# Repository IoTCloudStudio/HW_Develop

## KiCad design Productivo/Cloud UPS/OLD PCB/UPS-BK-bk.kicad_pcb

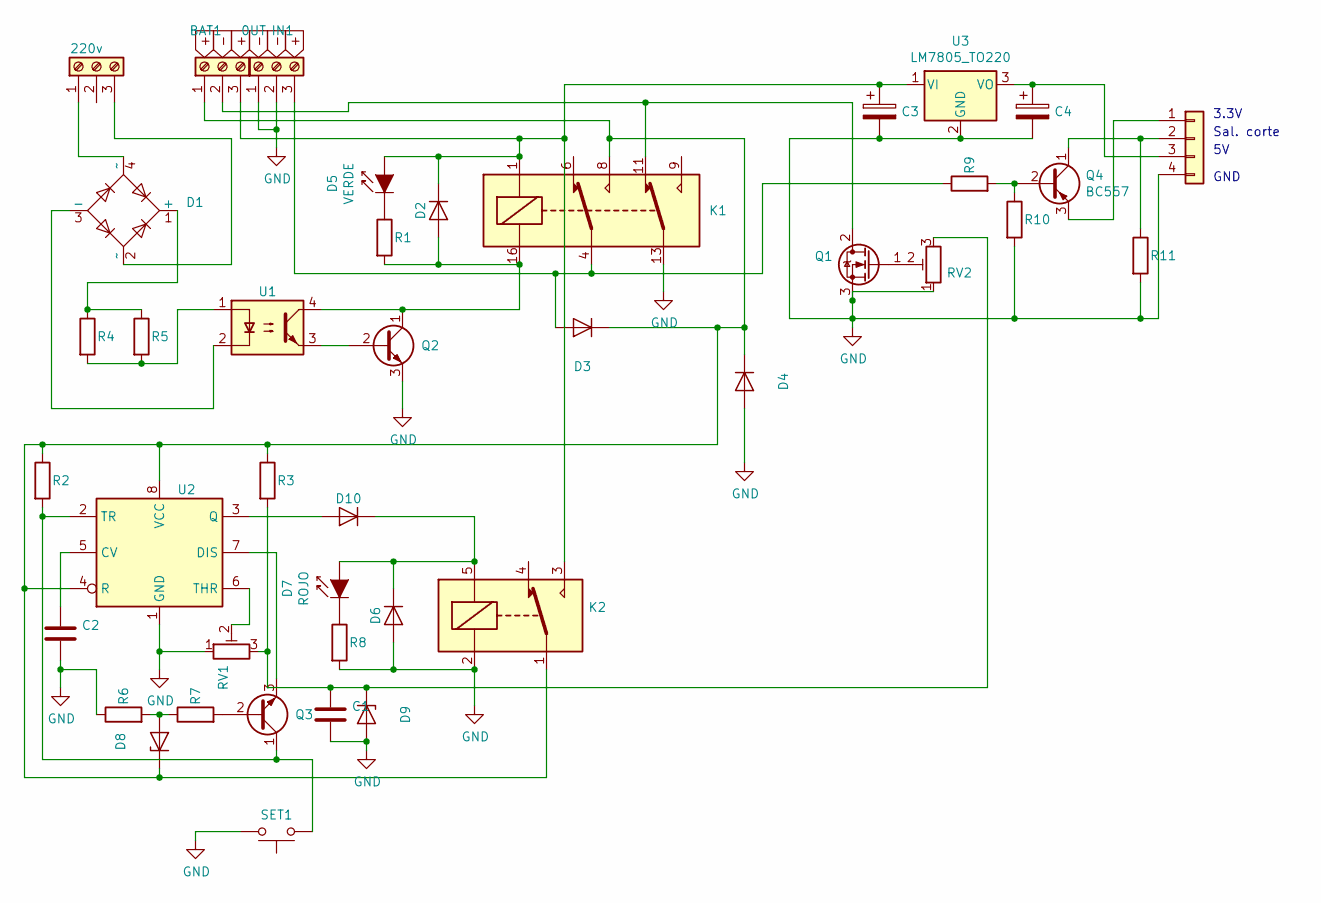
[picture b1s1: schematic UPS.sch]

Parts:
BAT1: 0UT; TerminalBlock_bornier-3_P5.08mm
C1: 100 Nf; C_Axial_L5.1mm_D3.1mm_P7.50mm_Horizontal
C2: 100nF; C_Axial_L5.1mm_D3.1mm_P7.50mm_Horizontal
C3: 33u; C_Radial_D5.0mm_H11.0mm_P2.00mm
C4: 1u; C_Radial_D5.0mm_H11.0mm_P2.00mm
D1: W10G; Diode_Bridge_Round_D9.8mm
D2, D6, D10: 1N4148; D_DO-35_SOD27_P7.62mm_Horizontal
D3, D4: 1N5408; D_DO-201AD_P15.24mm_Horizontal
D5: VERDE; LED_D3.0mm_IRBlack
D7: ROJO; LED_D3.0mm_IRBlack
D8, D9: D_Zener; D_DO-35_SOD27_P7.62mm_Horizontal
IN1: 12V; TerminalBlock_bornier-3_P5.08mm
J1: Conn_01x04; JST_EH_S4B-EH_1x04_P2.50mm_Horizontal
K1: G5V-2; Relay_DPDT_Omron_G5V-2
K2: SANYOU_SRD_Form_C; Relay_SPDT_SANYOU_SRD_Series_Form_C
Q1: IRF540N; TO-220-3_Vertical
Q2, Q3: BC548; TO-92_Inline
Q4: BC557; TO-92_Inline
R1: R; R_Axial_DIN0207_L6.3mm_D2.5mm_P2.54mm_Vertical
R2, R7, R8: 2K2; R_Axial_DIN0204_L3.6mm_D1.6mm_P1.90mm_Vertical
R3: 330; R_Axial_DIN0204_L3.6mm_D1.6mm_P1.90mm_Vertical
R4, R5: 68K; R_Axial_DIN0516_L15.5mm_D5.0mm_P5.08mm_Vertical
R6: 180; R_Axial_DIN0204_L3.6mm_D1.6mm_P1.90mm_Vertical
R9, R10, R11: 10k; R_Axial_DIN0207_L6.3mm_D2.5mm_P2.54mm_Vertical
RV1, RV2: R_POT_TRIM; Potentiometer_Bourns_3386P_Vertical
SET1: SW_Push; SW_SPST_CK_RS282G05A3
U1: PC817; DIP-4_W7.62mm
U2: NE555; DIP-8_W7.62mm_LongPads
U3: LM7805_TO220; TO-220-3_Vertical
j1: 220v; TerminalBlock_bornier-3_P5.08mm

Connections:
GND: C1.2, C2.2, C3.2, C4.2, D4.2 (A), D6.2 (A), D9.2 (A), IN1.1, IN1.2, J1.4, K1.13, K2.2, Q1.3 (S), Q2.3 (E), R6.1, R8.2, R10.2, R11.2, RV1.1, RV2.1, SET1.2, U2.1 (GND), U3.2 (GND); also elsewhere on the board
unnamed 1: BAT1.1, D3.1 (K), D4.1 (K), D8.1 (K), K1.8, K2.1, R2.1, R3.1, U2.4 (R), U2.8 (VCC); also elsewhere on the board
unnamed 2: BAT1.2, K1.11, Q1.2 (D); also elsewhere on the board
unnamed 3: BAT1.3, C3.1, D2.1 (K), D5.2 (A), K1.1, K2.3, U3.1 (VI); also elsewhere on the board
unnamed: C1.1, D9.1 (K), R3.2, RV1.3, RV2.3
unnamed: C2.1, U2.5 (CV)
unnamed: C4.1, J1.3, U3.3 (VO)
unnamed: D1.1 (+), R4.1, R5.1
unnamed: D1.2 (~~), j1.3
unnamed: D1.3 (-), U1.2
unnamed: D1.4 (~~), j1.1
unnamed 11: D2.2 (A), K1.16, Q2.1 (C), R1.2, U1.4; also elsewhere on the board
unnamed 12: D3.2 (A), IN1.3, K1.4, R9.1; also elsewhere on the board
unnamed: D5.1 (K), R1.1
unnamed: D7.1 (K), R8.1
unnamed: D8.2 (A), R6.2, R7.1
unnamed: D6.1 (K), D7.2 (A), D10.1 (K), K2.5
unnamed: D10.2 (A), U2.3 (Q)
unnamed: J1.1, Q4.3 (E)
unnamed: J1.2, Q4.1 (C), R11.1
unnamed: Q1.1 (G), RV2.2
unnamed: Q2.2 (B), U1.3
unnamed: Q3.1 (C), R2.2, SET1.1, U2.2 (TR)
unnamed: Q3.2 (B), R7.2
unnamed: Q3.3 (E), U2.7 (DIS)
unnamed: Q4.2 (B), R9.2, R10.1
unnamed: R4.2, R5.2, U1.1
unnamed: RV1.2, U2.6 (THR)

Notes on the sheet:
3.3V
Sal. corte
GND

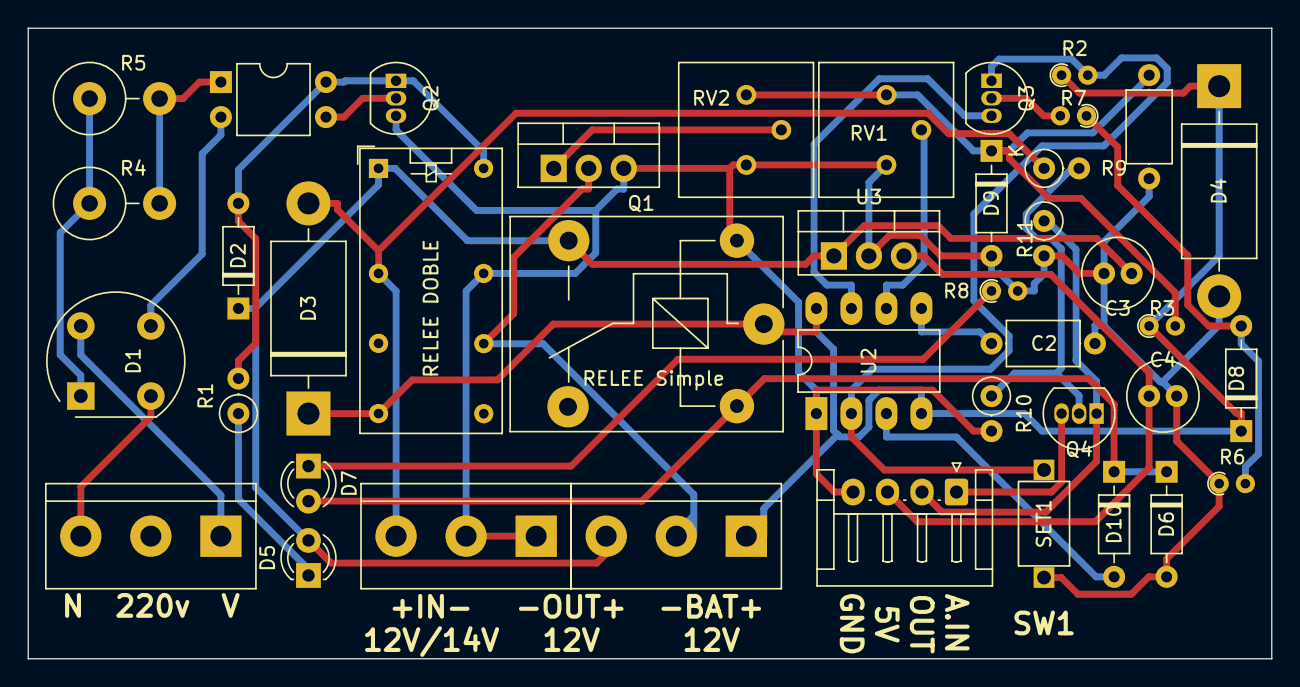
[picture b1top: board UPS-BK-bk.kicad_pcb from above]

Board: 2 copper layers, 90.2 x 45.7 mm, 41 parts (0 on the bottom side), 28 nets.

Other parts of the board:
RELEE DOBLE: G5V-2; Relay_DPDT_Omron_G5V-2

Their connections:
GND: RELEE DOBLE.13; also elsewhere on the board
unnamed 1: RELEE DOBLE.8; also elsewhere on the board
unnamed 2: RELEE DOBLE.11; also elsewhere on the board
unnamed 3: RELEE DOBLE.1; also elsewhere on the board
unnamed 11: RELEE DOBLE.16; also elsewhere on the board
unnamed 12: RELEE DOBLE.4; also elsewhere on the board

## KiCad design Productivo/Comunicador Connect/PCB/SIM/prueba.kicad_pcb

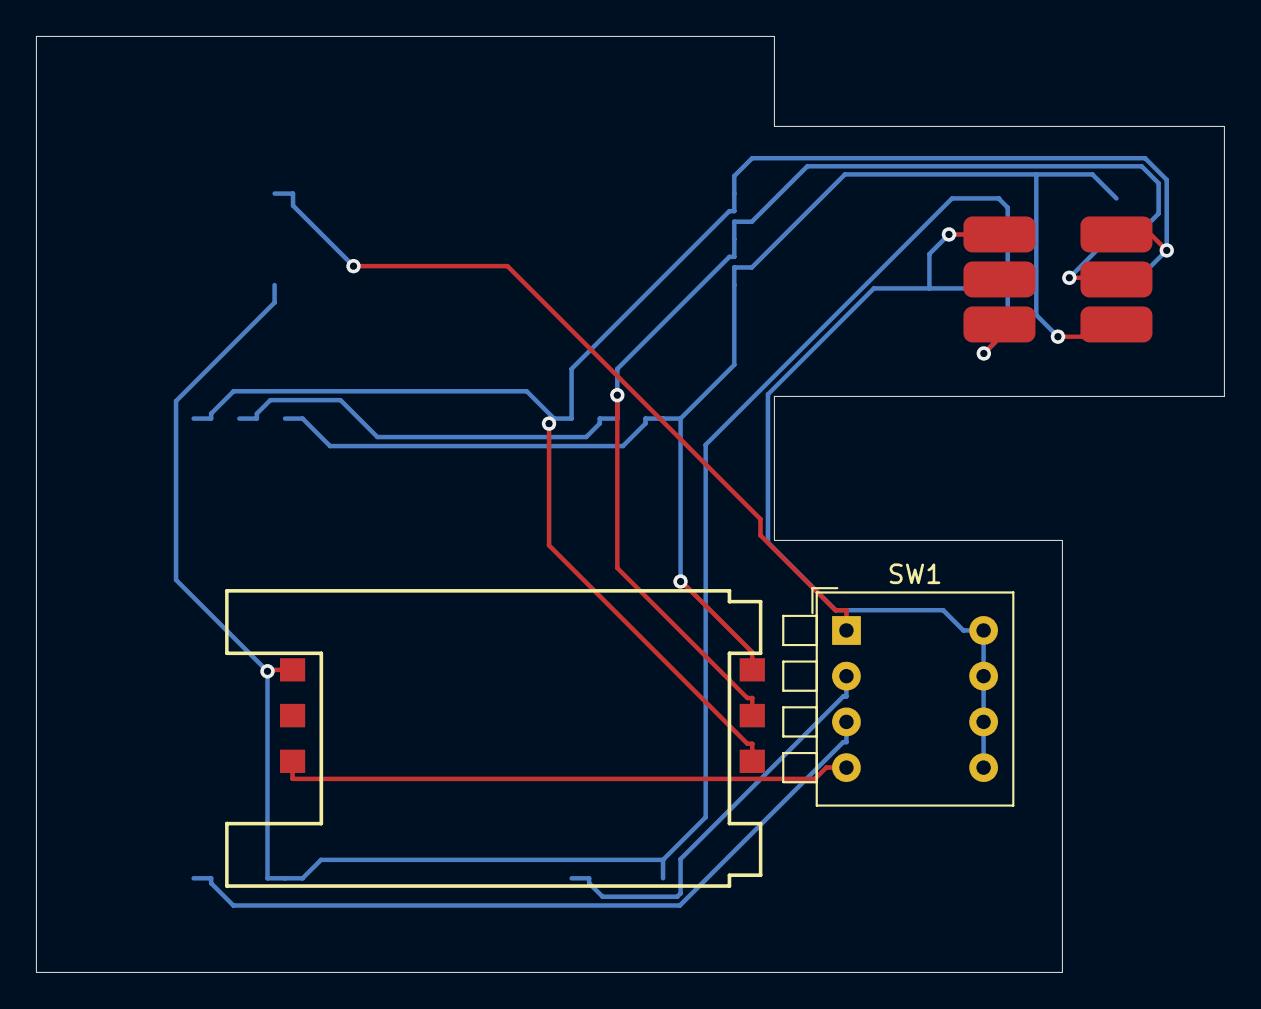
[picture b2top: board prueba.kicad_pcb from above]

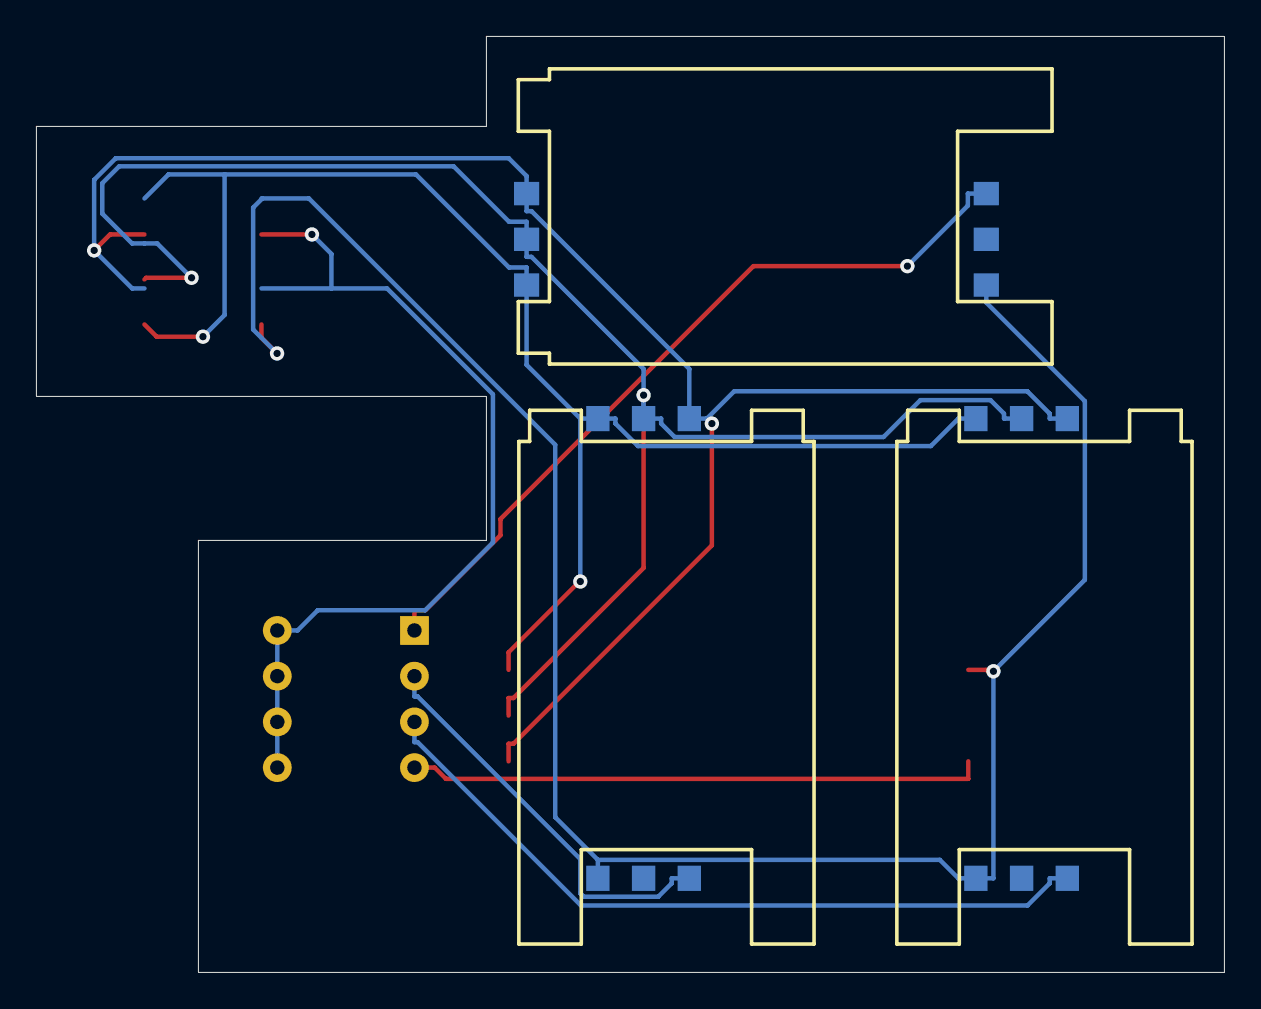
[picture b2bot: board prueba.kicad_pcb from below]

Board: 2 copper layers, 66.0 x 52.0 mm, 6 parts (3 on the bottom side), 9 nets.

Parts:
J1, J2, J3, J5: SIM5060-6-0-26-00-X_REVC; GCT_SIM5060-6-0-26-00-X_REVC1
J4: SIM_Card; SIM_CARD
SW1: SW_DIP_x04; SW_DIP_SPSTx04_Piano_10.8x11.72mm_W7.62mm_P2.54mm

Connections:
unnamed: J1.C1, J2.C1, J3.C1, J4.1, J5.C1
unnamed: J1.C2, J2.C2, J3.C2, J4.2, J5.C2
unnamed: J1.C3, J2.C3, J3.C3, J4.3, J5.C3
unnamed: J1.C5, J2.C5, J3.C5, J4.5, J5.C5
unnamed: J1.C7, SW1.1
unnamed: J2.C7, SW1.2
unnamed: J3.C7, SW1.3
unnamed: J4.7, SW1.5, SW1.6, SW1.7, SW1.8
unnamed: J5.C7, SW1.4

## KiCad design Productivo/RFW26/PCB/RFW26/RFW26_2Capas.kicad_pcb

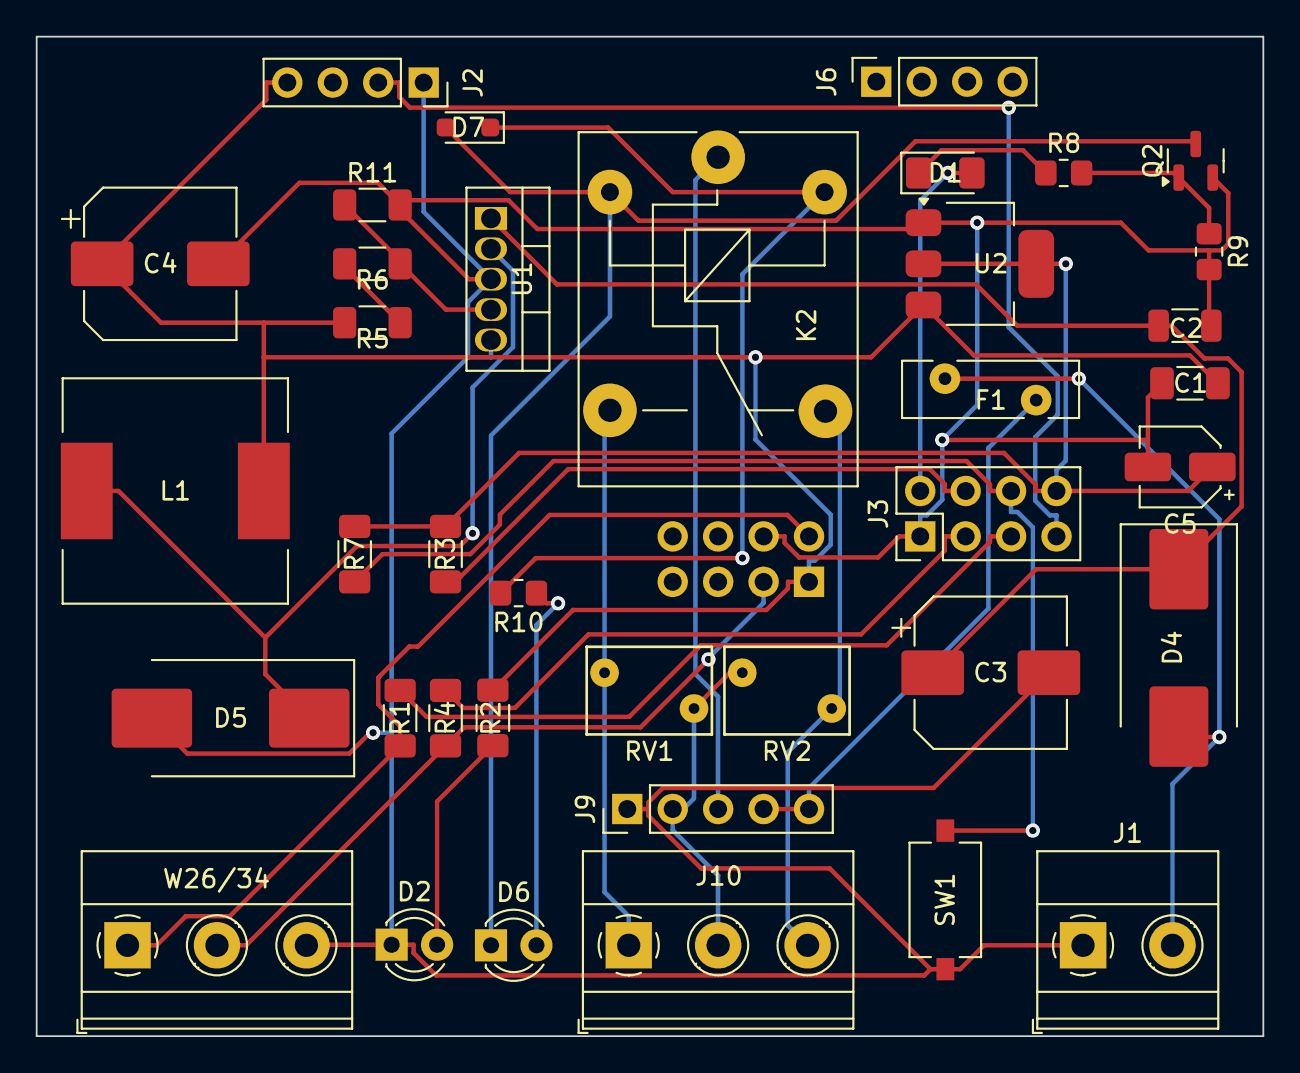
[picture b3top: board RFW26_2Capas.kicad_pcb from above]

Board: 2 copper layers, 68.6 x 55.9 mm, 39 parts (1 on the bottom side), 27 nets.

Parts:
C1: 0.1u; C_1206_3216Metric_Pad1.33x1.80mm_HandSolder
C2: 0.1u; C_1206_3216Metric
C3, C4: 220uF/35V; CP_Elec_8x10
C5: 10uF/16V; CP_Elec_4x4.5
D1: 1N4148; D_1206_3216Metric_Pad1.42x1.75mm_HandSolder
D2, D6: LED; LED_D3.0mm
D4, D5: SS34; D_SMC_Handsoldering
D7: 1N4148; D_SOD-323_HandSoldering
F1: MF-R110; Fuse_Bourns_MF-RHT100
J1: IN 12V; TerminalBlock_Phoenix_MKDS-1,5-2_1x02_P5.00mm_Horizontal
J2, J6: Receptor RF; PinSocket_1x04_P2.54mm_Vertical
J3: ESP01; PinHeader_2x04_P2.54mm_Vertical
J4: Conn_02x04_Counter_Clockwise; PinHeader_2x04_P2.54mm_Vertical
J9: jumpers salida; PinHeader_1x05_P2.54mm_Vertical
J10: OUT; TerminalBlock_Phoenix_MKDS-1,5-3_1x03_P5.00mm_Horizontal
K2: SANYOU_SRD_Form_C; Relay_SPDT_SANYOU_SRD_Series_Form_C
L1: 33 uH/3.5A; L_12x12mm_H8mm
Q2: MMBT5551L; SOT-23
R1, R2, R3, R5, R7: 10K; R_1206_3216Metric_Pad1.30x1.75mm_HandSolder
R4: 330; R_1206_3216Metric_Pad1.30x1.75mm_HandSolder
R6, R11: 4.7K; R_1206_3216Metric_Pad1.30x1.75mm_HandSolder
R8: 10K; R_0805_2012Metric_Pad1.20x1.40mm_HandSolder
R9: 100K; R_0805_2012Metric_Pad1.20x1.40mm_HandSolder
R10: 330; R_0805_2012Metric_Pad1.20x1.40mm_HandSolder
RV1, RV2: 470KD07; RV_Disc_D7mm_W4.9mm_P5mm
SW1: RESET; SW_Tactile_SPST_NO_Straight_CK_PTS636Sx25SMTRLFS
U1: LM2596S-5; TO-220-5_Vertical
U2: AMS1117-3.3; SOT-223-3_TabPin2
W26/34: Screw_Terminal_01x03; TerminalBlock_Phoenix_MKDS-1,5-3_1x03_P5.00mm_Horizontal

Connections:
12V: C2.1, C3.1, D4.1 (K), U1.1 (VIN)
12VOUT: F1.2, J9.4, J9.5
+3.3V: C5.1, J3.8, R3.1, R7.1, U2.2 (VO)
+5V: C1.2, C4.1, J2.4, J4.1, L1.2, R4.2, R5.2, U2.3 (VI)
D0: J4.3, R2.2, W26/34.2
D1: J4.2, R1.1, W26/34.1
GND: C1.1, C2.2, C3.2, C4.2, C5.2, D2.1 (K), D5.2 (A), J1.1, J2.1, J3.1, J4.4, J9.1, Q2.2 (E), R9.2, R11.1, SW1.1, U1.3 (GND), U1.5 (~ON/OFF), U2.1 (GND), W26/34.3
unnamed: D1.2 (A), J3.2
unnamed: D1.1 (K), R8.1
unnamed: D2.2 (A), R4.1
unnamed: D4.2 (A), F1.1, J1.2
unnamed: D5.1 (K), L1.1, U1.2 (OUT)
unnamed: D6.2 (A), R10.1
unnamed: D6.1 (K), D7.2 (A), K2.2, Q2.3 (C)
unnamed: D7.1 (K), K2.5, R10.2
unnamed: J2.2, J3.7
unnamed: J3.3, R2.1
unnamed: J3.4, R3.2
unnamed: J3.5, R1.2
unnamed: J3.6, R7.2, SW1.2
unnamed: J9.3, K2.1
unnamed: J10.1, K2.3, RV1.1
unnamed: J9.2, J10.2, RV1.2, RV2.1
unnamed: J10.3, K2.4, RV2.2
unnamed: Q2.1 (B), R8.2, R9.1
unnamed: R5.1, R6.2
unnamed: R6.1, R11.2, U1.4 (FB)
